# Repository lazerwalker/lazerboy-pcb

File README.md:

# Game Boy Button PCB

This is a PCB that fits into a Nintendo DMG-1 (1989 Game Boy) shell. It's designed to take in button input, with traces that fit the original button placement, and route them to a convenient 9-pin output (4-way d-pad, A/B/Start/Select buttons, common ground). In my case, I connect them directly to the GPIO of a Raspberry Pi Zero.

It's based on Rolf's [DMG-Rolf](http://gbdev.gg8.se/files/schematics/DMG-Rolf/) project, but far simplified since this board contains only button contacts and no actual logic.

## License

This work is licensed under the Creative Commons Attribution-NonCommercial-ShareAlike 2.5 Canada License. To view a copy of this license, visit http://creativecommons.org/licenses/by-nc-sa/2.5/ca/ or send a letter to Creative Commons, 444 Castro Street, Suite 900, Mountain View, California, 94041, USA.

If you have any questions, comments, or concerns, please email the original creator of these files at chrisweird@gmail.com, or the creator of this derivative project at gb@lazerwalker.com

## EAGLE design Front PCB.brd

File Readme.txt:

This work is licensed under the Creative Commons Attribution-NonCommercial-ShareAlike 2.5 Canada License. To view a copy of this license, visit http://creativecommons.org/licenses/by-nc-sa/2.5/ca/ or send a letter to Creative Commons, 444 Castro Street, Suite 900, Mountain View, California, 94041, USA.

If you have any questions, comments, or concerns, please email the original creator of these files at chrisweird@gmail.com

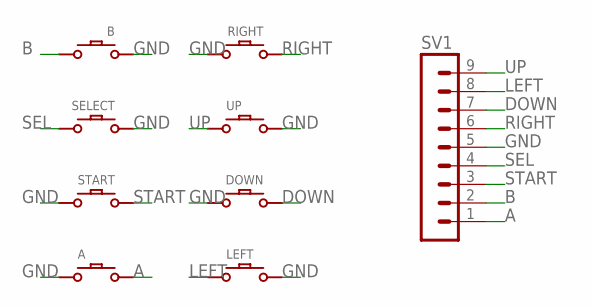
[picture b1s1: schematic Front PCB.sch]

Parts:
A: DMG-BTN
B: DMG-BTN
DOWN: DMG-BTN
LEFT: DMG-BTN
RIGHT: DMG-BTN
SELECT: DMG-BTN; DMG-SEL
START: DMG-BTN; DMG-ST
SV1: MA09-1
UP: DMG-BTN

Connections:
A: A.P$2, SV1.1
B: B.P$2, SV1.2
DOWN: DOWN.P$1, SV1.7
GND: A.P$1, B.P$1, DOWN.P$2, LEFT.P$2, RIGHT.P$2, SELECT.P$1, START.P$2, SV1.5, UP.P$2
LEFT: LEFT.P$1, SV1.8
RIGHT: RIGHT.P$1, SV1.6
SEL: SELECT.P$2, SV1.4
START: START.P$1, SV1.3
UP: SV1.9, UP.P$1

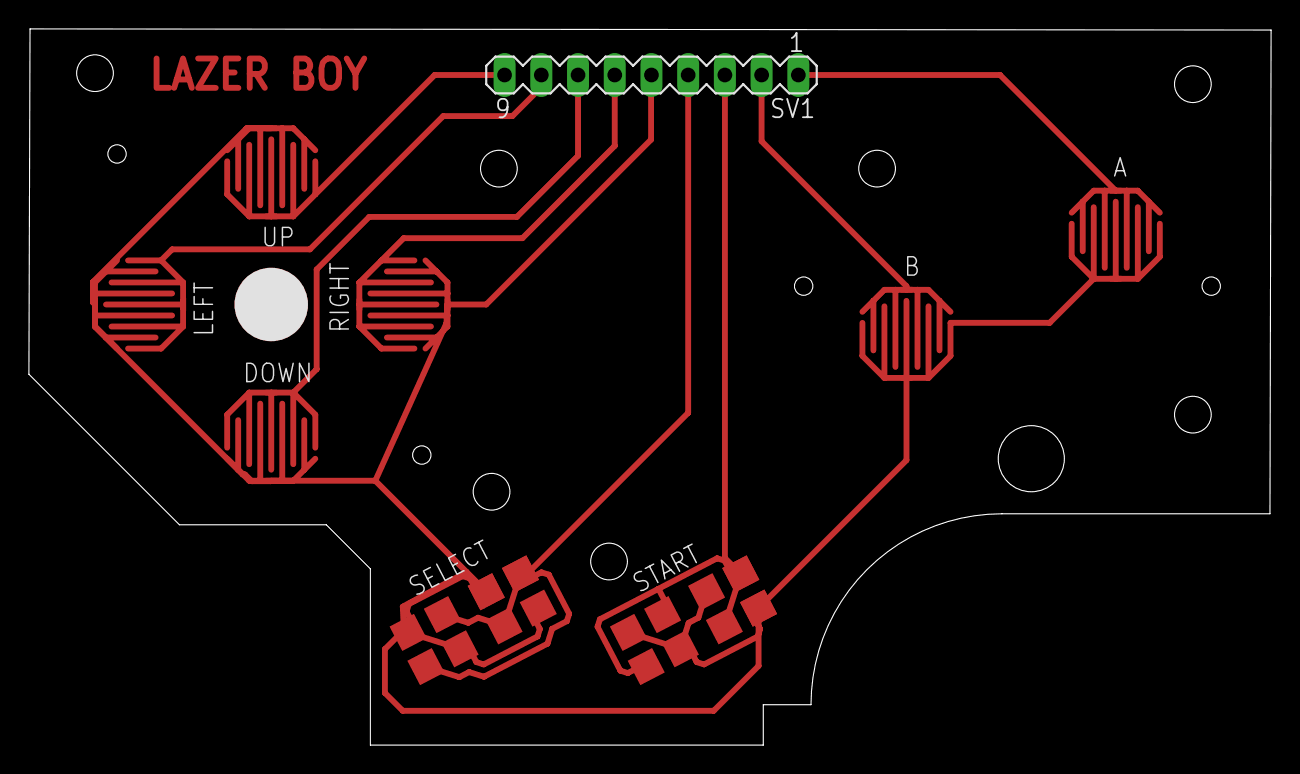
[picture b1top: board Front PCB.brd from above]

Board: 2 copper layers, 85.9 x 49.5 mm, 9 parts (0 on the bottom side), 9 nets.

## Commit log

2016-05-06 Gitignore temporary eagle files
2016-05-06 Remove unused boards
2016-05-06 Add .DS_Store to gitignore
2016-05-06 Remove more temp files
2016-05-07 Redesign board to use through-hole pins
2016-05-07 Crop slightly on top
    To avoid collisions with the screen I'm using. Longer forehead was
    necessary when there were horizontal headers sticking out.
2016-05-07 Try making small holes smaller
2017-10-06 Show the picture in the README
